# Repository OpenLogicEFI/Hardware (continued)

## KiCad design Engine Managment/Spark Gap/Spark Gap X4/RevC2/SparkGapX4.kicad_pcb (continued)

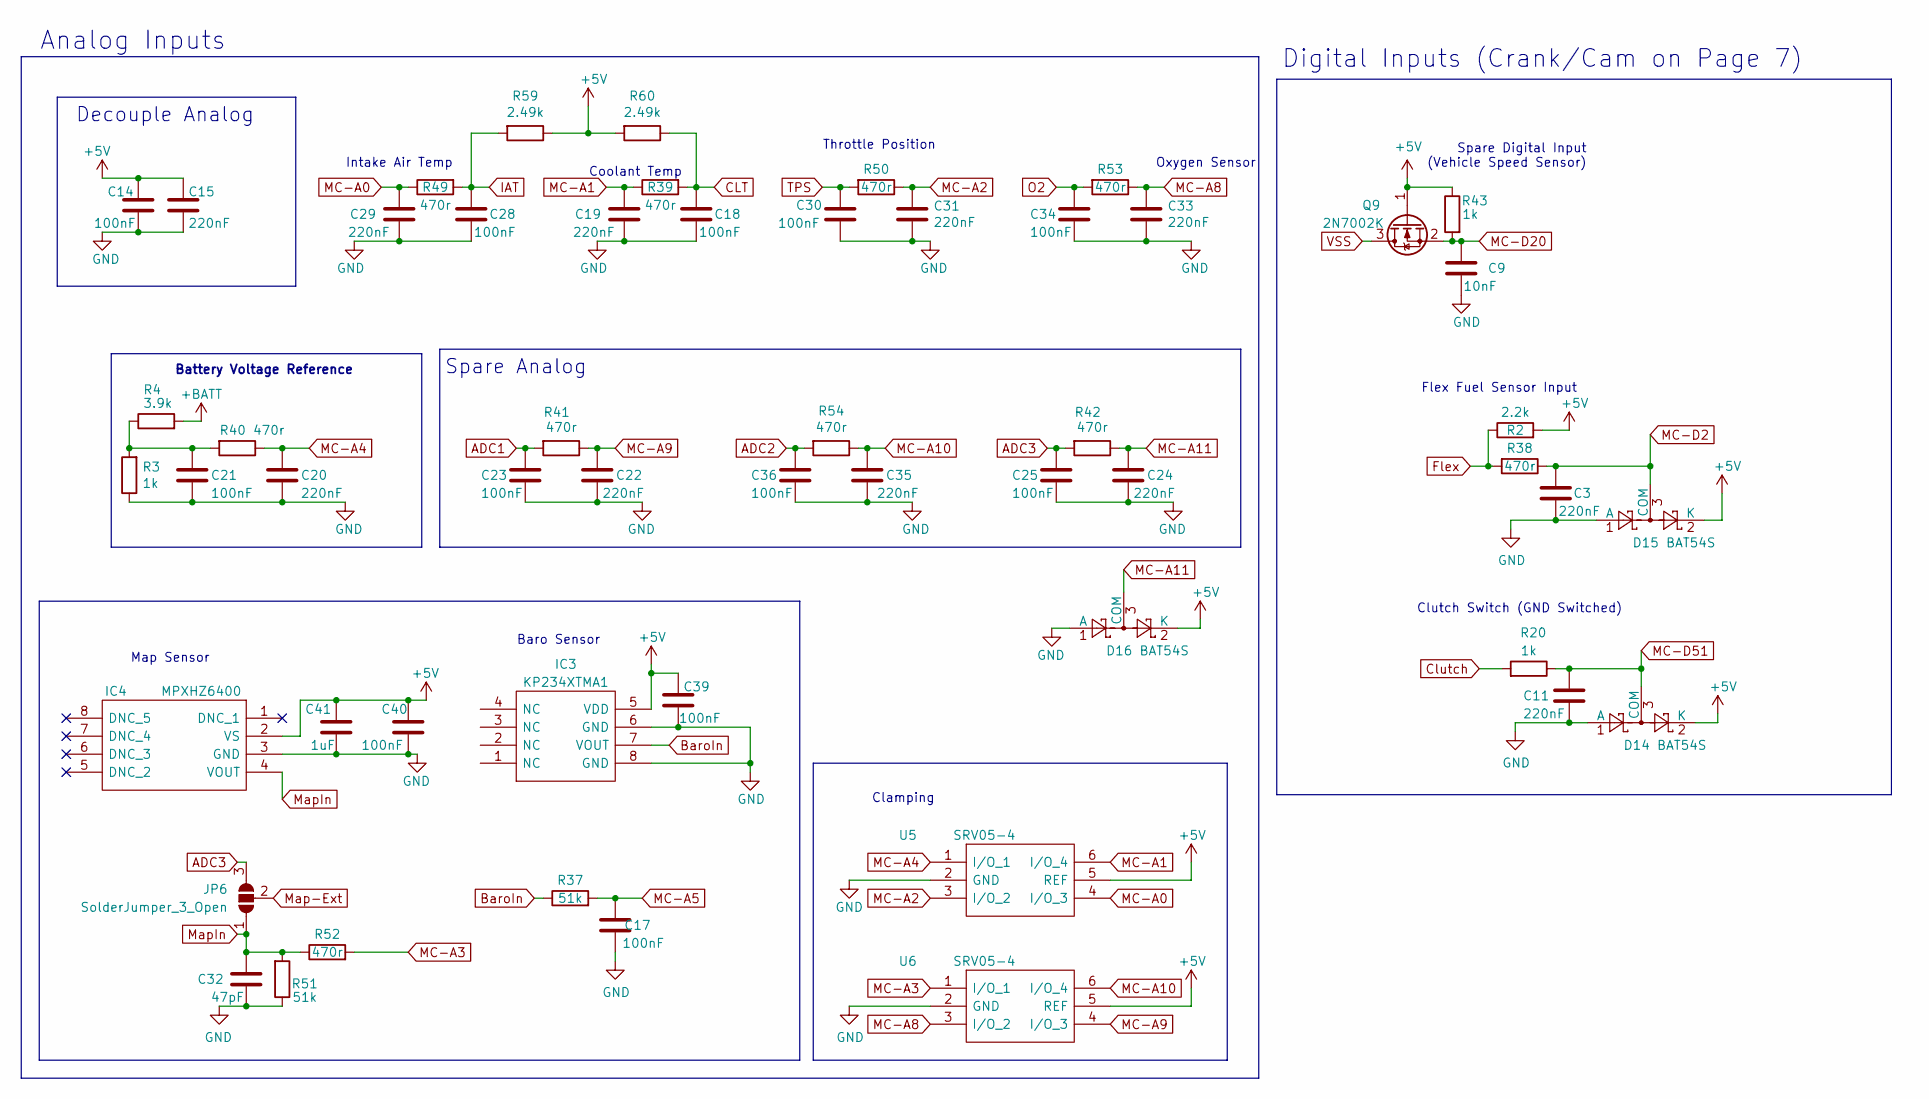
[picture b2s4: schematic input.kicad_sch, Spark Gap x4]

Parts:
C3, C11, C15, C19, C20, C22, C24, C29, C31, C33, C35: 220nF; C_0402_1005Metric; Manufacture Part Number CL05B224KO5NNNC; LCSC C16772
C9: 10nF; C_0402_1005Metric; Manufacture Part Number CL05B103KB5NNNC; LCSC C15195
C14, C17, C18, C21, C23, C25, C28, C30, C34, C36, C39, C40: 100nF; C_0402_1005Metric; Manufacture Part Number CL05B104KB54PNC; LCSC C307331
C32: 47pF; C_0402_1005Metric; Manufacture Part Number 0402CG470J500NT; LCSC C1567
C41: 1uF; C_0402_1005Metric; Manufacture Part Number CL05A105KA5NQNC; LCSC C52923
D14, D15, D16: BAT54S; SOT-23; Manufacture Part Number BAT54S; LCSC C7420333
IC3: KP234XTMA1; KP234-Handsoldering
IC4: MPXHZ6400; MPXHxxx_Handsoldering
JP6: SolderJumper_3_Open; SolderJumper-3-OPEN
Q9: 2N7002K; SOT-23; LCSC C22379475
R2: 2.2k; R_0402_1005Metric; Manufacture Part Number 0402WGF2201TCE; LCSC C25879
R3: 1k; R_0603_1608Metric; Manufacture Part Number 0603WAF1001T5E; LCSC C21190
R4: 3.9k; R_0603_1608Metric; Manufacture Part Number 0603WAF3901T5E; LCSC C23018
R20, R43: 1k; R_0402_1005Metric; Manufacture Part Number 0402WGF1001TCE; LCSC C11702
R37, R51: 51k; R_0402_1005Metric; Manufacture Part Number 0402WGF5102TCE; LCSC C25794
R38, R39, R40, R41, R42, R49, R50, R52, R53, R54: 470r; R_0402_1005Metric; Manufacture Part Number 0402WGF4700TCE; LCSC C25117
R59, R60: 2.49k; R_Axial_DIN0207_L6.3mm_D2.5mm_P7.62mm_Horizontal
U5, U6: SRV05-4; SOT-23-6; LCSC C2836319

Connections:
+5V: C14.1, C15.1, C39.1, C40.1, C41.1, D14.2 (K), D15.2 (K), D16.2 (K), IC3.5 (VDD), IC4.2 (VS), Q9.1 (G), R2.2, R43.1, R59.1, R60.2, U5.5 (REF), U6.5 (REF); also elsewhere on the board
+BATT: R4.2; also elsewhere on the board
ADC1: C23.1, R41.2; also elsewhere on the board
ADC2: C36.1, R54.2; also elsewhere on the board
ADC3: C25.1, JP6.3 (B), R42.2
BaroIn: IC3.7 (VOUT), R37.1
CLT: C18.1, R39.2, R60.1; also elsewhere on the board
Clutch: R20.2; also elsewhere on the board
Flex: R2.1, R38.2; also elsewhere on the board
GND: C3.2, C9.2, C11.2, C14.2, C15.2, C17.2, C18.2, C19.2, C20.2, C21.2, C22.2, C23.2, C24.2, C25.2, C28.2, C29.2, C30.2, C31.2, C32.2, C33.2, C34.2, C35.2, C36.2, C39.2, C40.2, C41.2, D14.1 (A), D15.1 (A), D16.1 (A), IC3.6 (GND), IC3.8 (GND), IC4.3 (GND), R3.1, R51.1, U5.2 (GND), U6.2 (GND); also elsewhere on the board
IAT: C28.1, R49.2, R59.2; also elsewhere on the board
MC-A0: C29.1, R49.1, U5.4 (I/O_3); also elsewhere on the board
MC-A1: C19.1, R39.1, U5.6 (I/O_4); also elsewhere on the board
MC-A2: C31.1, R50.1, U5.3 (I/O_2); also elsewhere on the board
MC-A3: R52.2, U6.1 (I/O_1); also elsewhere on the board
MC-A4: C20.1, R40.1, U5.1 (I/O_1); also elsewhere on the board
MC-A5: C17.1, R37.2; also elsewhere on the board
MC-A8: C33.1, R53.1, U6.3 (I/O_2); also elsewhere on the board
MC-A9: C22.1, R41.1, U6.4 (I/O_3); also elsewhere on the board
MC-A10: C35.1, R54.1, U6.6 (I/O_4); also elsewhere on the board
MC-A11: C24.1, D16.3 (COM), R42.1; also elsewhere on the board
MC-D2: C3.1, D15.3 (COM), R38.1; also elsewhere on the board
MC-D20: C9.1, Q9.2 (S), R43.2; also elsewhere on the board
MC-D51: C11.1, D14.3 (COM), R20.1; also elsewhere on the board
Map-Ext: JP6.2 (C); also elsewhere on the board
MapIn: C32.1, IC4.4 (VOUT), JP6.1 (A), R51.2, R52.1
unnamed: C21.1, R3.2, R4.1, R40.2
O2: C34.1, R53.2; also elsewhere on the board
TPS: C30.1, R50.2; also elsewhere on the board
VSS: Q9.3 (D); also elsewhere on the board

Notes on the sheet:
Map Sensor
Clutch Switch (GND Switched)
Analog Inputs
Throttle Position
Spare Digital Input (Vehicle Speed Sensor)
Oxygen Sensor
Digital Inputs (Crank/Cam on Page 7)
Coolant Temp
Intake Air Temp
Baro Sensor
Battery Voltage Reference
Spare Analog
Flex Fuel Sensor Input
Decouple Analog
Clamping

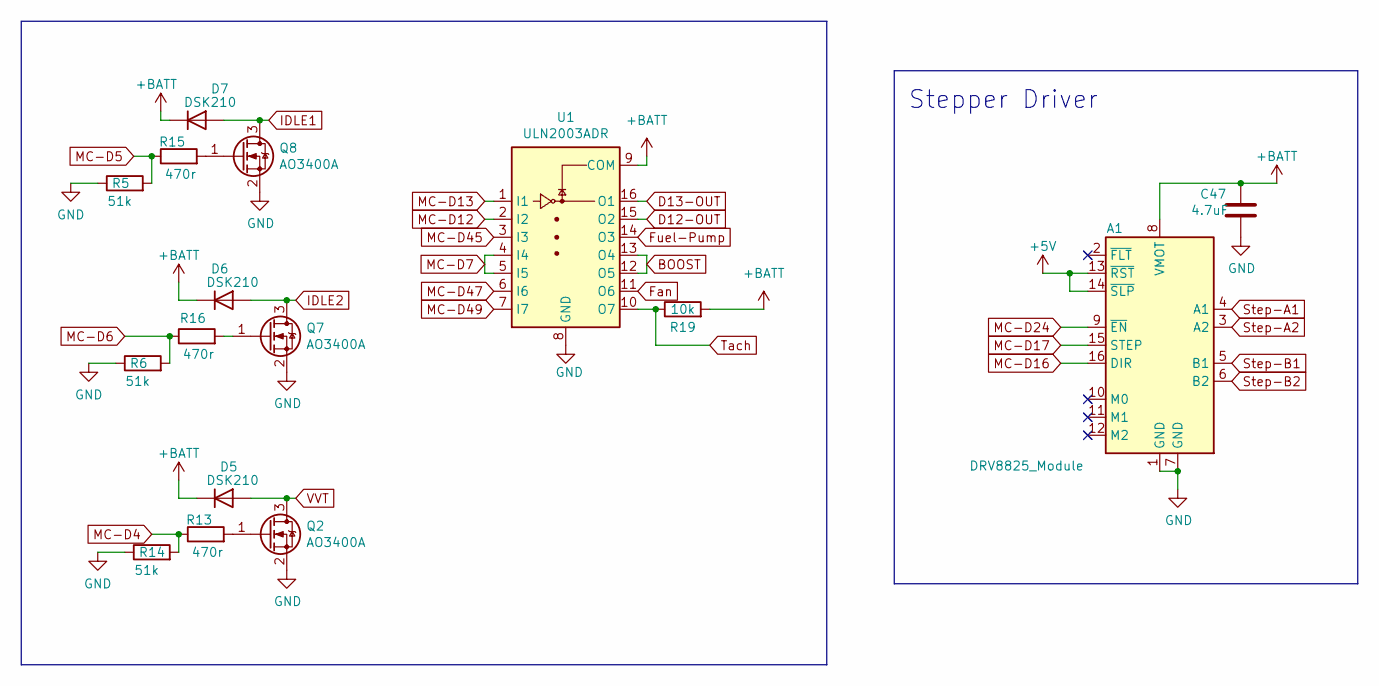
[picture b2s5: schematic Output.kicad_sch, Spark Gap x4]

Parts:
A1: DRV8825_Module; DVR8825-Labeled-Front
C47: 4.7uF; C_1206_3216Metric; Manufacture Part Number 1206B475K500NT; LCSC C29823
D5, D6, D7: DSK210; D_SOD-123F; Manufacture Part Number DSK210; LCSC C7502713
Q2, Q7, Q8: AO3400A; SOT-23; LCSC C20917
R5, R6, R14: 51k; R_0402_1005Metric; Manufacture Part Number 0402WGF5102TCE; LCSC C25794
R13, R15, R16: 470r; R_0402_1005Metric; Manufacture Part Number 0402WGF4700TCE; LCSC C25117
R19: 10k; R_0402_1005Metric; Manufacture Part Number 0402WGF1002TCE; LCSC C25744
U1: ULN2003ADR; SOIC-16_3.9x9.9mm_P1.27mm; Manufacture Part Number ULN2003ADR; LCSC C7512

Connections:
+5V: A1.13 (~RST), A1.14 (~SLP); also elsewhere on the board
+BATT: A1.8 (VMOT), C47.1, D5.1 (K), D6.1 (K), D7.1 (K), R19.2, U1.9 (COM); also elsewhere on the board
BOOST: U1.12 (O5), U1.13 (O4); also elsewhere on the board
D12-OUT: U1.15 (O2); also elsewhere on the board
D13-OUT: U1.16 (O1); also elsewhere on the board
Fan: U1.11 (O6); also elsewhere on the board
Fuel-Pump: U1.14 (O3); also elsewhere on the board
GND: A1.1 (GND), A1.7 (GND), C47.2, Q2.2 (S), Q7.2 (S), Q8.2 (S), R5.1, R6.1, R14.1, U1.8 (GND); also elsewhere on the board
IDLE1: A1.6 (B2), D7.2 (A), Q8.3 (D); also elsewhere on the board
IDLE2: A1.5 (B1), D6.2 (A), Q7.3 (D); also elsewhere on the board
MC-D4: R13.1, R14.2; also elsewhere on the board
MC-D5: R5.2, R15.1; also elsewhere on the board
MC-D6: R6.2, R16.1; also elsewhere on the board
MC-D7: U1.4 (I4), U1.5 (I5); also elsewhere on the board
MC-D12: U1.2 (I2); also elsewhere on the board
MC-D13: U1.1 (I1); also elsewhere on the board
MC-D16: A1.16 (DIR); also elsewhere on the board
MC-D17: A1.15 (STEP); also elsewhere on the board
MC-D24: A1.9 (~EN); also elsewhere on the board
MC-D45: U1.3 (I3); also elsewhere on the board
MC-D47: U1.6 (I6); also elsewhere on the board
MC-D49: U1.7 (I7); also elsewhere on the board
unnamed: Q2.1 (G), R13.2
unnamed: Q7.1 (G), R16.2
unnamed: Q8.1 (G), R15.2
Step-A1: A1.4 (A1); also elsewhere on the board
Step-A2: A1.3 (A2); also elsewhere on the board
Tach: R19.1, U1.10 (O7); also elsewhere on the board
VVT: D5.2 (A), Q2.3 (D); also elsewhere on the board

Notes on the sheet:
Stepper Driver

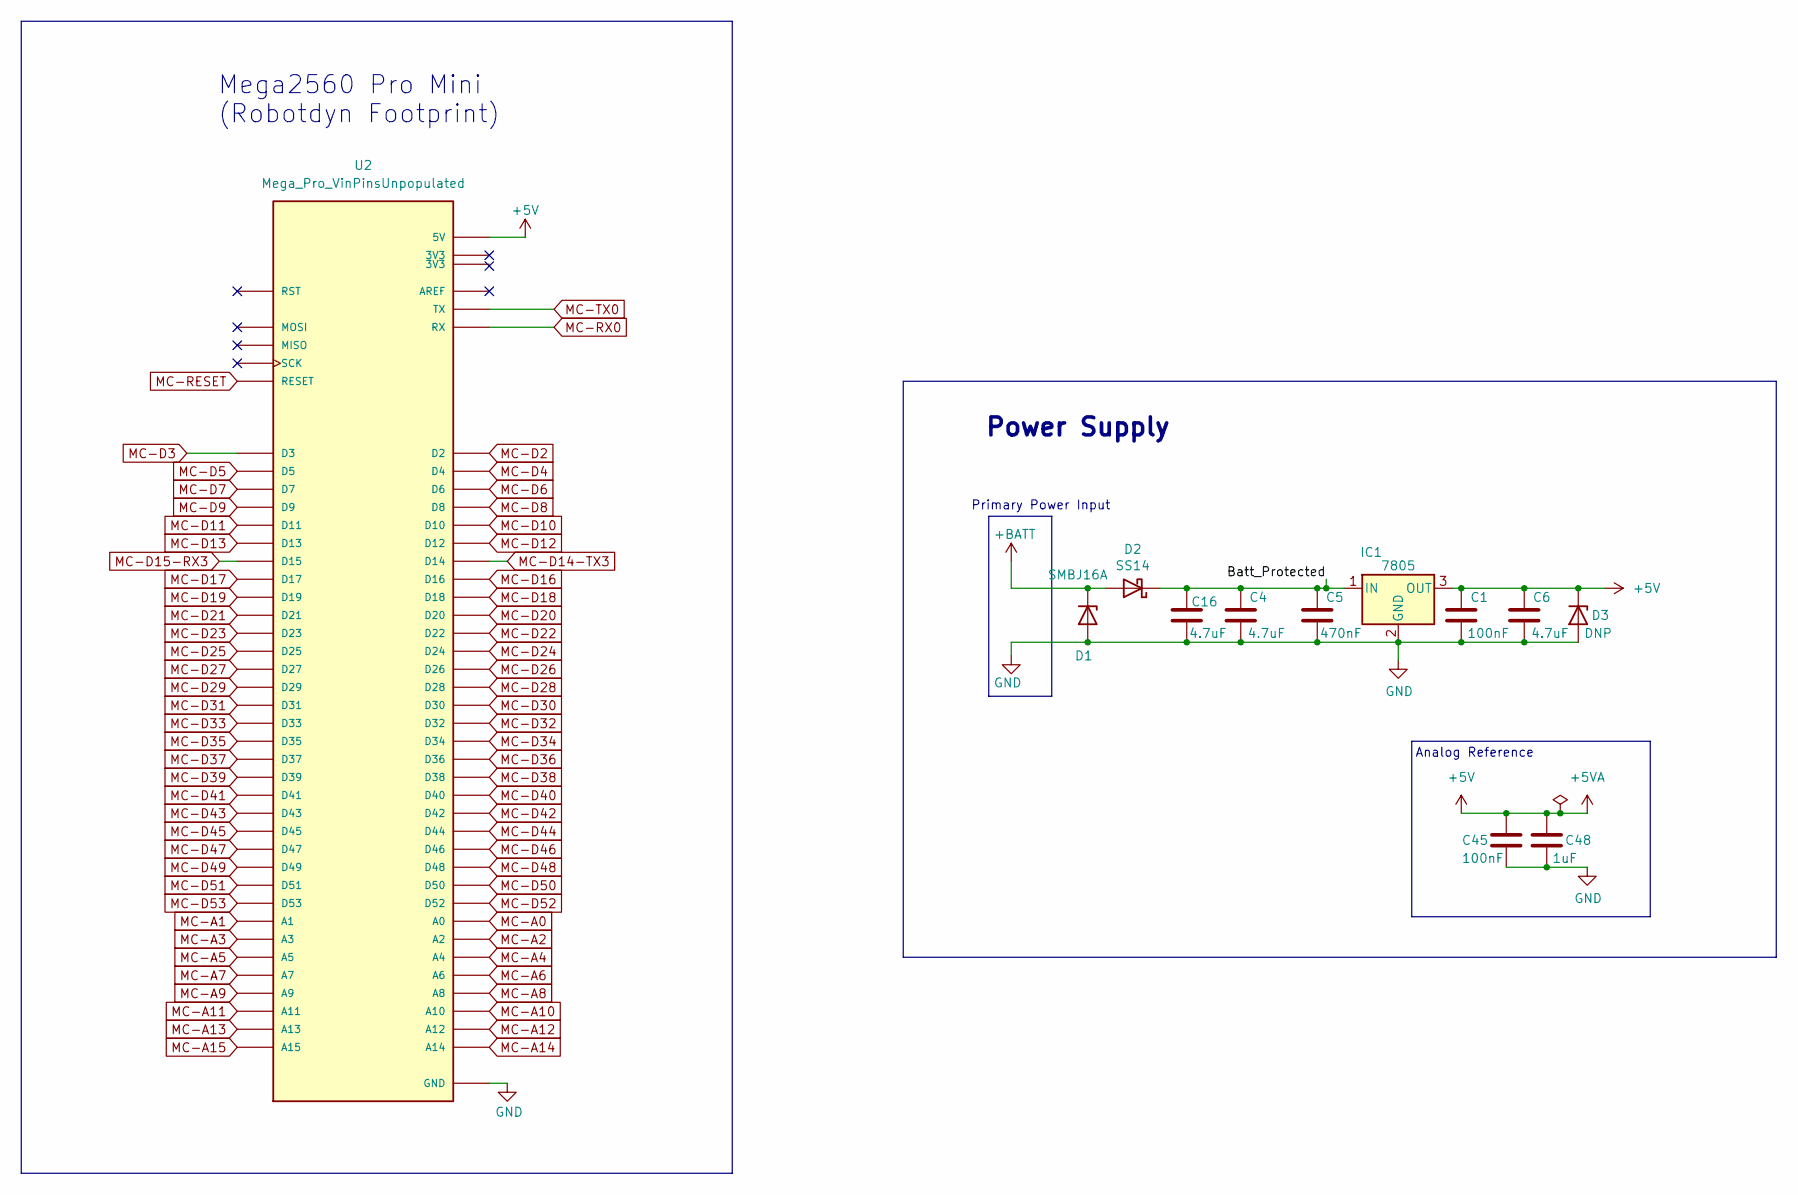
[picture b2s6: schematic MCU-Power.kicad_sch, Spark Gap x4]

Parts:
C1, C45: 100nF; C_0402_1005Metric; Manufacture Part Number CL05B104KB54PNC; LCSC C307331
C4, C6, C16: 4.7uF; C_1206_3216Metric; Manufacture Part Number 1206B475K500NT; LCSC C29823
C5: 470nF; C_0805_2012Metric; Manufacture Part Number CL21B474KBFNNNE; LCSC C13967
C48: 1uF; C_0402_1005Metric; Manufacture Part Number CL05A105KA5NQNC; LCSC C52923
D1: SMBJ16A; D_SMB; Manufacture Part Number SMBJ16A; LCSC C19077571
D2: SS14; D_SMA; Manufacture Part Number SS14; LCSC C2480
D3: DNP; D_SOD-323; Manufacture Part Number MMSZ5232BS; LCSC C22395563
IC1: 7805; TO-220-3_Vertical_SmallCrtYrd
U2: Mega_Pro_VinPinsUnpopulated; Arduino_Mega_Mini_2560_SmallCrtYd_NoVin

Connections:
+5V: C1.1, C6.1, C45.1, C48.1, D3.1 (K), IC1.3 (OUT), U2.5V_1 (5V), U2.5V_2 (5V), U2.5V_3 (5V); also elsewhere on the board
+BATT: D1.1 (K), D2.2 (A); also elsewhere on the board
/MCU and Power/Batt_Protected: C4.1, C5.1, C16.1, D2.1 (K), IC1.1 (IN)
GND: C1.2, C4.2, C5.2, C6.2, C16.2, C45.2, C48.2, D1.2 (A), D3.2 (A), IC1.2 (GND), U2.GND_1 (GND), U2.GND_2 (GND), U2.GND_3 (GND); also elsewhere on the board
MC-A0: U2.A0; also elsewhere on the board
MC-A1: U2.A1; also elsewhere on the board
MC-A2: U2.A2; also elsewhere on the board
MC-A3: U2.A3; also elsewhere on the board
MC-A4: U2.A4; also elsewhere on the board
MC-A5: U2.A5; also elsewhere on the board
MC-A6: U2.A6
MC-A7: U2.A7
MC-A8: U2.A8; also elsewhere on the board
MC-A9: U2.A9; also elsewhere on the board
MC-A10: U2.A10; also elsewhere on the board
MC-A11: U2.A11; also elsewhere on the board
MC-A12: U2.A12
MC-A13: U2.A13
MC-A14: U2.A14
MC-A15: U2.A15
MC-D2: U2.D2; also elsewhere on the board
MC-D3: U2.D3; also elsewhere on the board
MC-D4: U2.D4; also elsewhere on the board
MC-D5: U2.D5; also elsewhere on the board
MC-D6: U2.D6; also elsewhere on the board
MC-D7: U2.D7; also elsewhere on the board
MC-D8: U2.D8; also elsewhere on the board
MC-D9: U2.D9; also elsewhere on the board
MC-D10: U2.D10; also elsewhere on the board
MC-D11: U2.D11; also elsewhere on the board
MC-D12: U2.D12; also elsewhere on the board
MC-D13: U2.D13; also elsewhere on the board
MC-D14-TX3: U2.D14; also elsewhere on the board
MC-D15-RX3: U2.D15; also elsewhere on the board
MC-D16: U2.D16; also elsewhere on the board
MC-D17: U2.D17; also elsewhere on the board
MC-D18: U2.D18; also elsewhere on the board
MC-D19: U2.D19; also elsewhere on the board
MC-D20: U2.D20; also elsewhere on the board
MC-D21: U2.D21
MC-D22: U2.D22
MC-D23: U2.D23
MC-D24: U2.D24; also elsewhere on the board
MC-D25: U2.D25
MC-D26: U2.D26
MC-D27: U2.D27
MC-D28: U2.D28
MC-D29: U2.D29
MC-D30: U2.D30
MC-D31: U2.D31
MC-D32: U2.D32
MC-D33: U2.D33
MC-D34: U2.D34
MC-D35: U2.D35
MC-D36: U2.D36
MC-D37: U2.D37
MC-D38: U2.D38; also elsewhere on the board
MC-D39: U2.D39
MC-D40: U2.D40; also elsewhere on the board
MC-D41: U2.D41
MC-D42: U2.D42
MC-D43: U2.D43
MC-D44: U2.D44
MC-D45: U2.D45; also elsewhere on the board
MC-D46: U2.D46
MC-D47: U2.D47; also elsewhere on the board
MC-D48: U2.D48
MC-D49: U2.D49; also elsewhere on the board
MC-D50: U2.D50; also elsewhere on the board
MC-D51: U2.D51; also elsewhere on the board
MC-D52: U2.D52; also elsewhere on the board
MC-D53: U2.D53
MC-RESET: U2.RESET; also elsewhere on the board
MC-RX0: U2.RX; also elsewhere on the board
MC-TX0: U2.TX; also elsewhere on the board

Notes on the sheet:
Primary Power Input
Power Supply
Analog Reference
Mega2560 Pro Mini (Robotdyn Footprint)

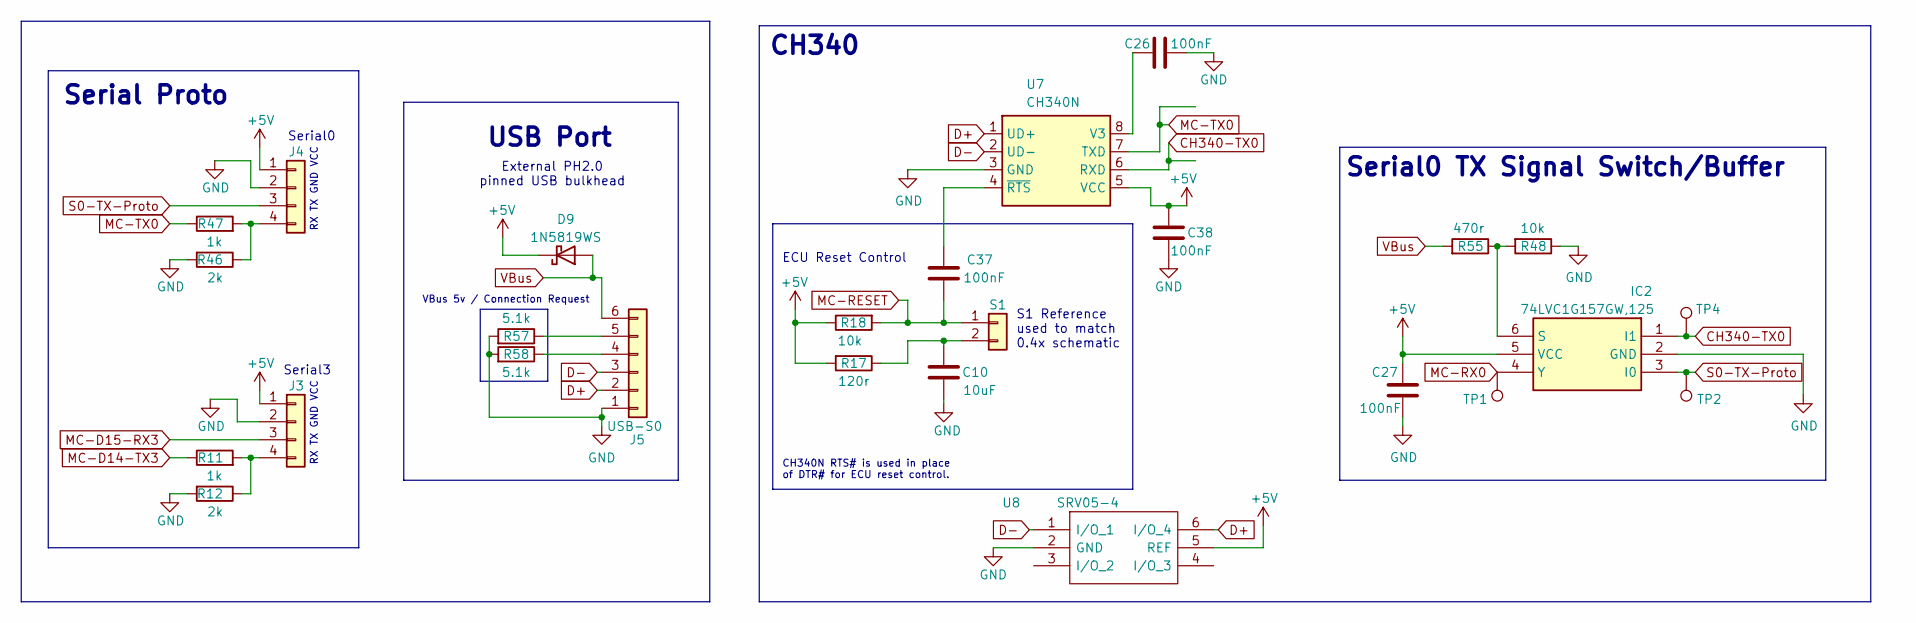
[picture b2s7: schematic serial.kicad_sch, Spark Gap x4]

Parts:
C10: 10uF; C_0603_1608Metric; Manufacture Part Number CL10A106KP8NNNC; LCSC C19702
C26, C27, C37, C38: 100nF; C_0402_1005Metric; Manufacture Part Number CL05B104KB54PNC; LCSC C307331
D9: 1N5819WS; D_SOD-323; Manufacture Part Number 1N5819WS; LCSC C7420326
IC2: 74LVC1G157GW,125; SOP65P210X110-6N; Manufacture Part Number 74LVC1G157GW,125; LCSC C135822
J3, J4: Conn_01x04; 1X4-PROTO-NoSilk
J5: USB-S0; JST_PH_B6B-PH-K_1x06_P2.00mm_Vertical
R11, R47: 1k; R_0402_1005Metric; Manufacture Part Number 0402WGF1001TCE; LCSC C11702
R12, R46: 2k; R_0402_1005Metric; Manufacture Part Number 0402WGF2001TCE; LCSC C4109
R17: 120r; R_0603_1608Metric; Manufacture Part Number 0402WGF4700TCE; LCSC C22787
R18, R48: 10k; R_0402_1005Metric; Manufacture Part Number 0402WGF1002TCE; LCSC C25744
R55: 470r; R_0402_1005Metric; Manufacture Part Number 0402WGF4700TCE; LCSC C25117
R57, R58: 5.1k; R_0402_1005Metric; Manufacture Part Number 0402WGF5101TCE; LCSC C25905
S1: Reset Control; PinHeader_1x02_P2.54mm_Horizontal
TP1, TP2, TP4: TestPoint; TestPoint_THT_D0.6mm_Drill0.3mm
U7: CH340N; SOIC-8_3.9x4.9mm_P1.27mm; LCSC C2977777
U8: SRV05-4; SOT-23-6; LCSC C2836319

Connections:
+5V: C27.2, C38.1, D9.1 (K), IC2.5 (VCC), J3.1, J4.1, R17.2, R18.1, U7.5 (VCC), U8.5 (REF); also elsewhere on the board
CH340-TX0: IC2.1 (I1), TP4.1 (1_1), U7.6 (RXD)
D+: J5.2, U7.1 (UD+), U8.6 (I/O_4)
D-: J5.3, U7.2 (UD-), U8.1 (I/O_1)
GND: C10.2, C26.2, C27.1, C38.2, IC2.2 (GND), J3.2, J4.2, J5.1, R12.2, R46.2, R48.1, R57.2, R58.2, U7.3 (GND), U8.2 (GND); also elsewhere on the board
MC-D14-TX3: R11.1; also elsewhere on the board
MC-D15-RX3: J3.3; also elsewhere on the board
MC-RESET: C37.2, R18.2, S1.1; also elsewhere on the board
MC-RX0: IC2.4 (Y), TP1.1 (1_1); also elsewhere on the board
MC-TX0: R47.1, U7.7 (TXD); also elsewhere on the board
unnamed: IC2.6 (S), R48.2, R55.1
unnamed: J3.4, R11.2, R12.1
unnamed: J4.4, R46.1, R47.2
unnamed: J5.4, R58.1
unnamed: J5.5, R57.1
unnamed: C10.1, R17.1, S1.2
unnamed: C26.1, U7.8 (V3)
unnamed: C37.1, U7.4 (~RTS)
S0-TX-Proto: IC2.3 (I0), J4.3, TP2.1 (1_1)
VBus: D9.2 (A), J5.6, R55.2

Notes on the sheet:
CH340
RX TX GND VCC
Serial3
S1 Reference used to match 0.4x schematic
External PH2.0 pinned USB bulkhead
Serial0
ECU Reset Control
VBus 5v / Connection Request
Serial0 TX Signal Switch/Buffer
USB Port
CH340N RTS# is used in place of DTR# for ECU reset control.
Serial Proto

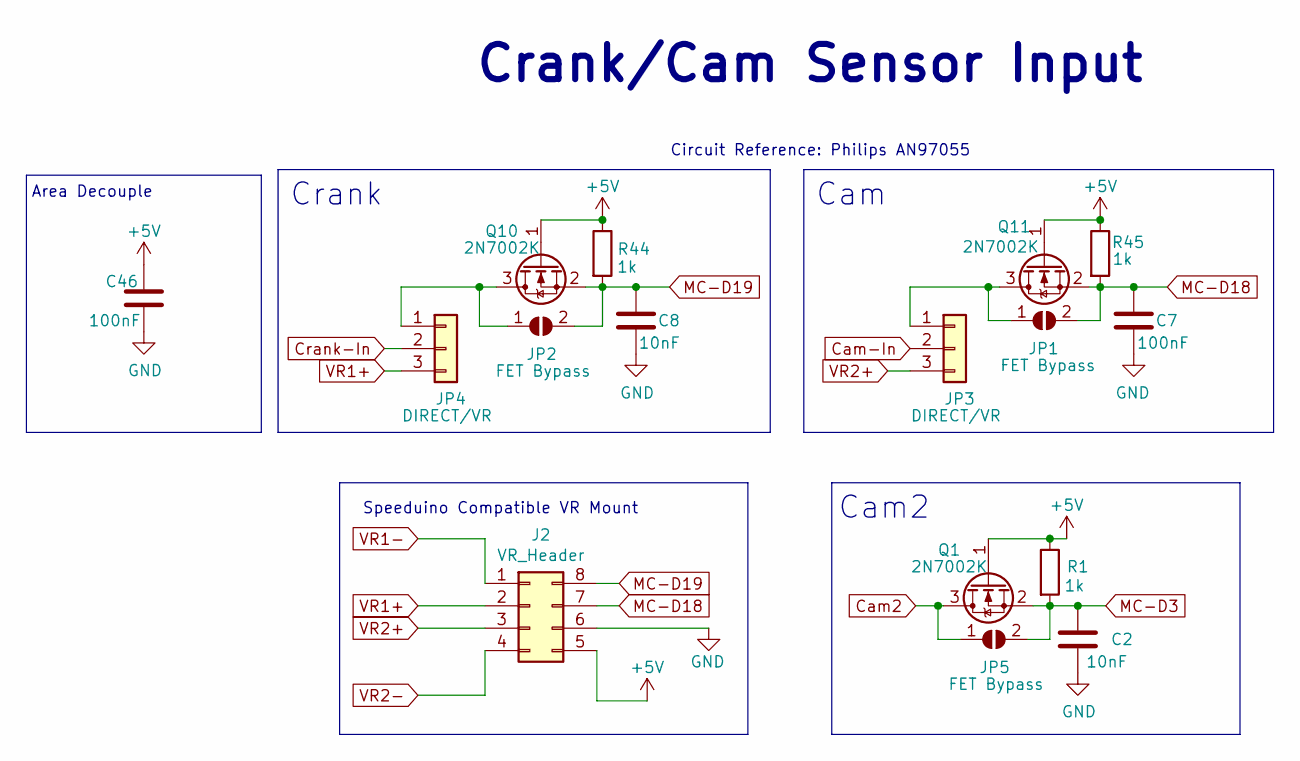
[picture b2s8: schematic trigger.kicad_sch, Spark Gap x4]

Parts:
C2, C8: 10nF; C_0402_1005Metric; Manufacture Part Number CL05B103KB5NNNC; LCSC C15195
C7, C46: 100nF; C_0402_1005Metric; Manufacture Part Number CL05B104KB54PNC; LCSC C307331
J2: VR_Header; Socket_VRConditioner_Corrected
JP1, JP2, JP5: FET Bypass; SolderJumper-2_P1.3mm_Open_RoundedPad1.0x1.5mm
JP3, JP4: DIRECT/VR; 1x03-Proto
Q1, Q10, Q11: 2N7002K; SOT-23; LCSC C22379475
R1, R44, R45: 1k; R_0402_1005Metric; Manufacture Part Number 0402WGF1001TCE; LCSC C11702

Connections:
+5V: C46.1, J2.5, Q1.1 (G), Q10.1 (G), Q11.1 (G), R1.1, R44.1, R45.1; also elsewhere on the board
Cam2: JP5.1 (A), Q1.3 (D); also elsewhere on the board
Cam-In: JP3.2; also elsewhere on the board
Crank-In: JP4.2; also elsewhere on the board
GND: C2.1, C7.1, C8.1, C46.2, J2.6; also elsewhere on the board
MC-D3: C2.2, JP5.2 (B), Q1.2 (S), R1.2; also elsewhere on the board
MC-D18: C7.2, J2.7, JP1.2 (B), Q11.2 (S), R45.2; also elsewhere on the board
MC-D19: C8.2, J2.8, JP2.2 (B), Q10.2 (S), R44.2; also elsewhere on the board
unnamed: JP1.1 (A), JP3.1, Q11.3 (D)
unnamed: JP2.1 (A), JP4.1, Q10.3 (D)
VR1+: J2.2, JP4.3
VR1-: J2.1; also elsewhere on the board
VR2+: J2.3, JP3.3
VR2-: J2.4; also elsewhere on the board

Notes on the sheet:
Crank/Cam Sensor Input
Cam2
Cam
Speeduino Compatible VR Mount
Area Decouple
Circuit Reference: Philips AN97055
Crank

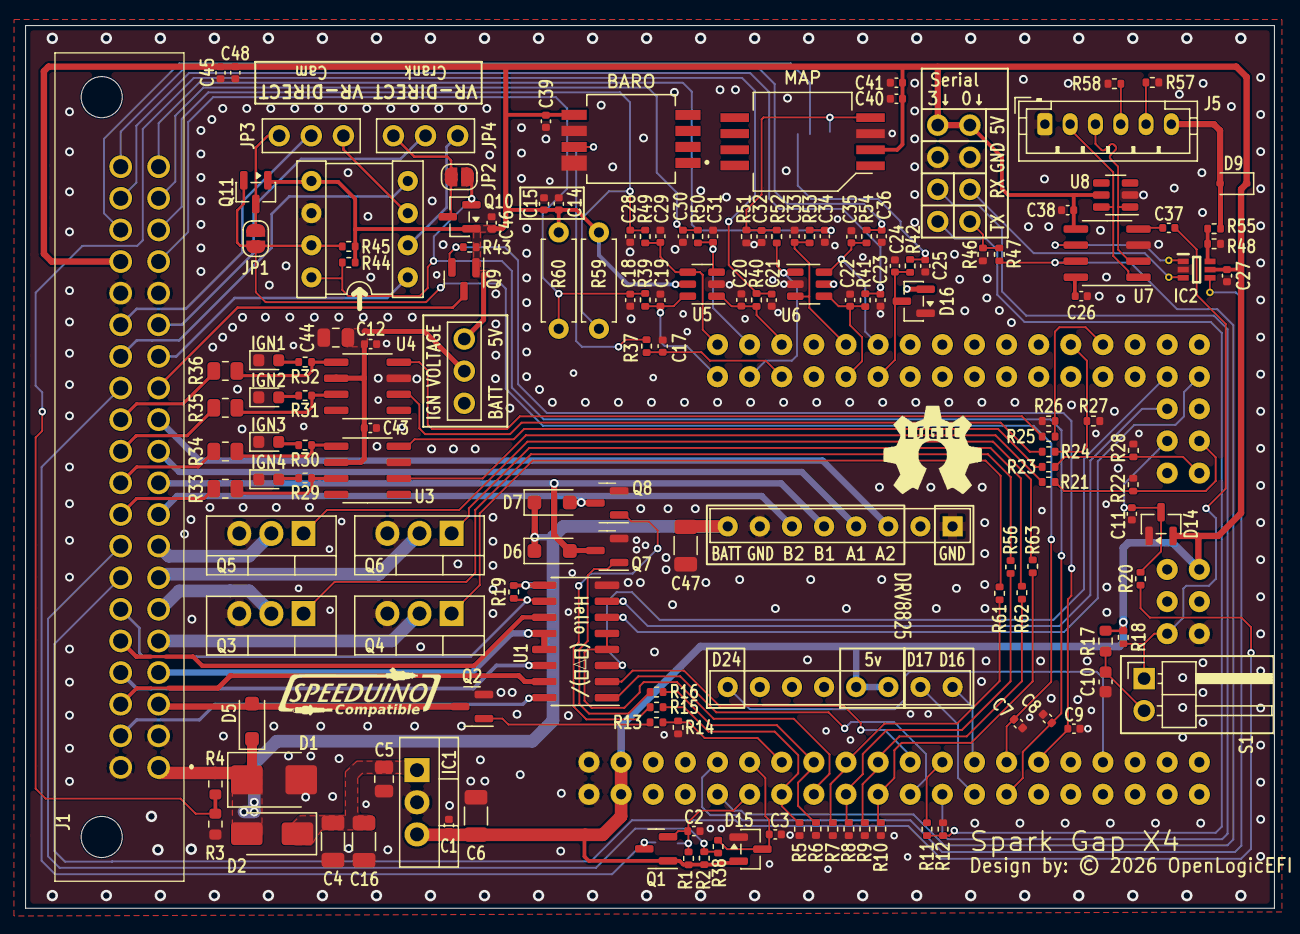
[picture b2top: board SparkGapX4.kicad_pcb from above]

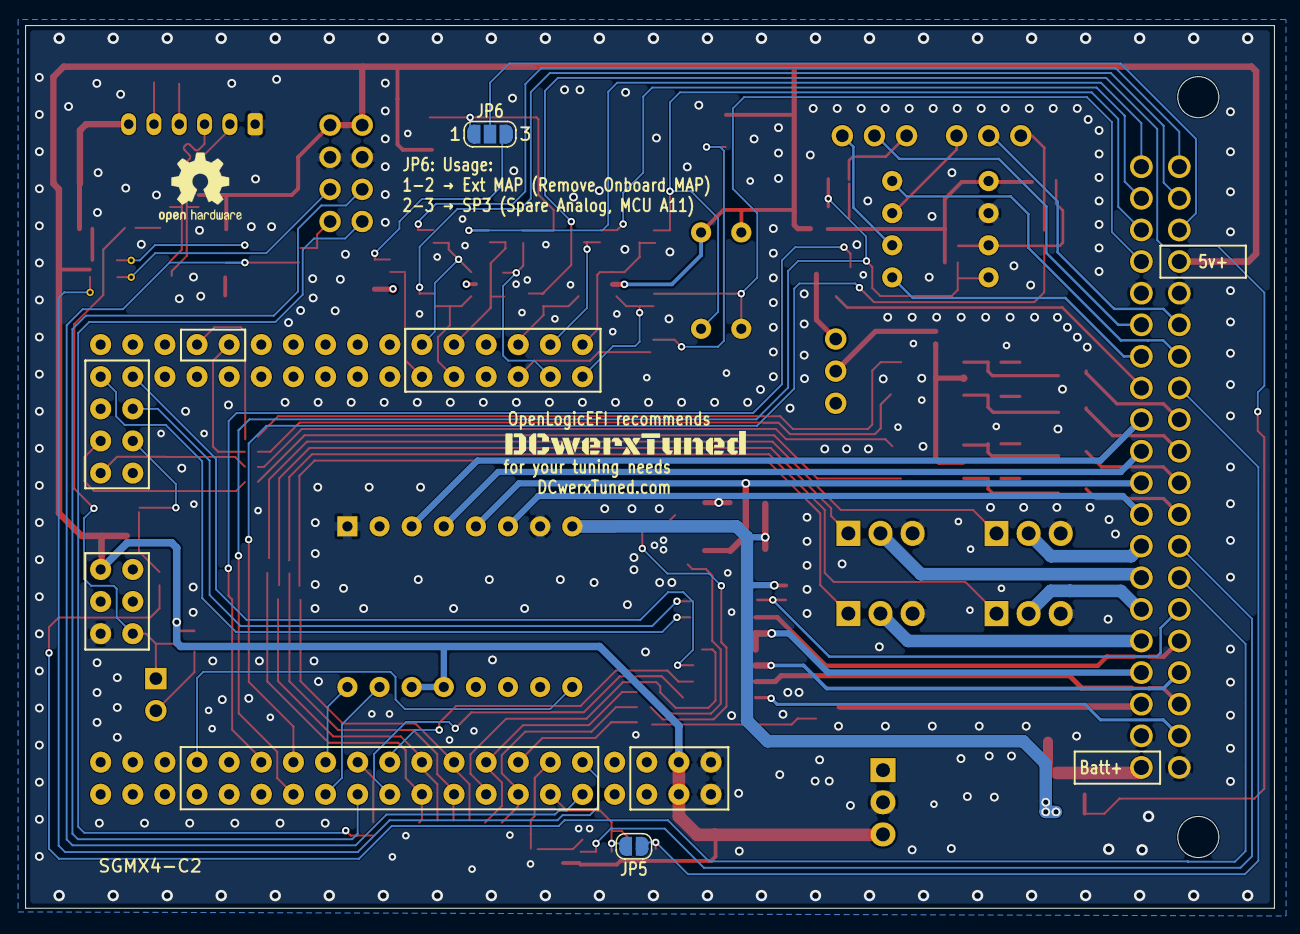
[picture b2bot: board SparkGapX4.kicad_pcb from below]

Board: 4 copper layers, 98.8 x 69.8 mm, 164 parts (3 on the bottom side), 120 nets.

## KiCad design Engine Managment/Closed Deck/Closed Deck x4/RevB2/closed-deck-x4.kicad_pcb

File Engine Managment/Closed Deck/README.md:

# ClosedDeck

ClosedDeck is a hardware shield designed to use an Arduino Mega as the central microcontroller unit (MCU), thereby enabling it to operate as a standalone engine management system. This functionality is achieved when the shield is coupled with compatible firmware from an open-source project called Speeduino, developed by Josh Stewart.

www.OpenLogicEFI.com

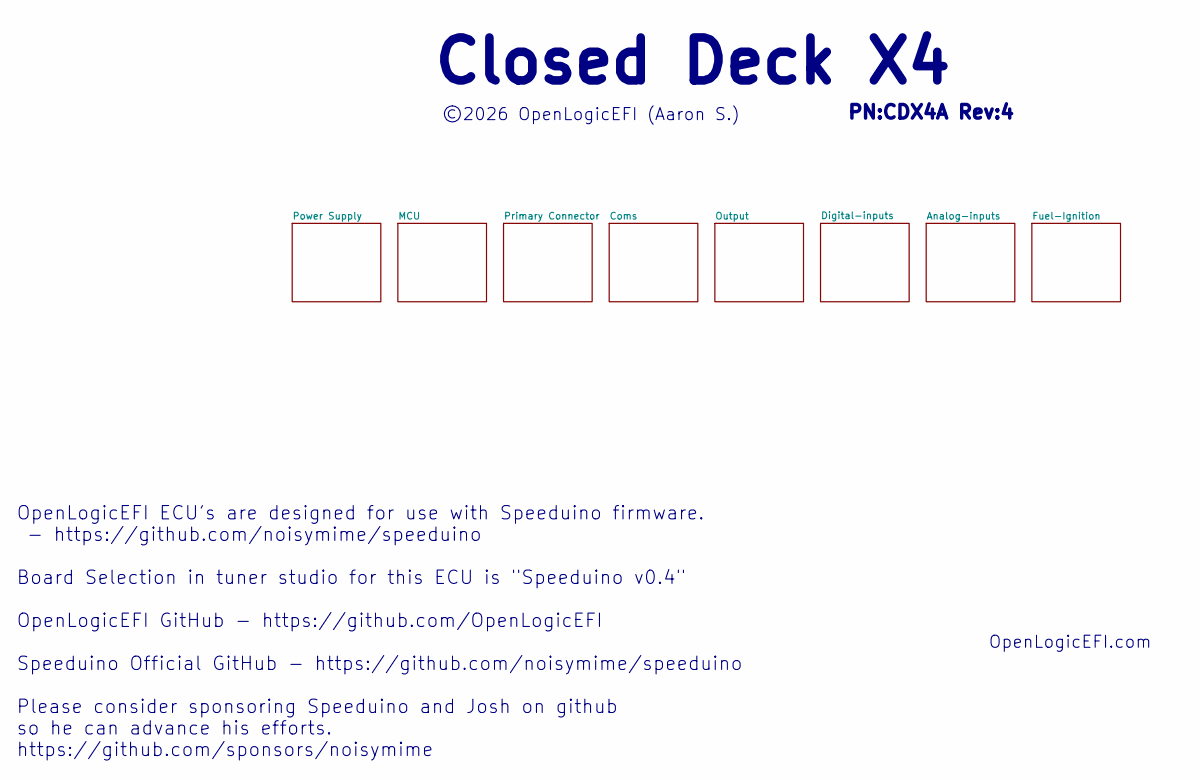
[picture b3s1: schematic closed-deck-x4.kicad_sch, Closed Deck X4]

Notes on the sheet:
©2026 OpenLogicEFI (Aaron S.)
OpenLogicEFI ECU's are designed for use with Speeduino firmware. - https://github.com/noisymime/speeduino Board Selection in tuner studio for this ECU is "Speeduino v0.4" OpenLogicEFI GitHub - https://github.com/OpenLogicEFI Speeduino Official GitHub - https://github.com/noisymime/speeduino Please 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
Closed Deck X4
PN:CDX4A Rev:4
OpenLogicEFI.com

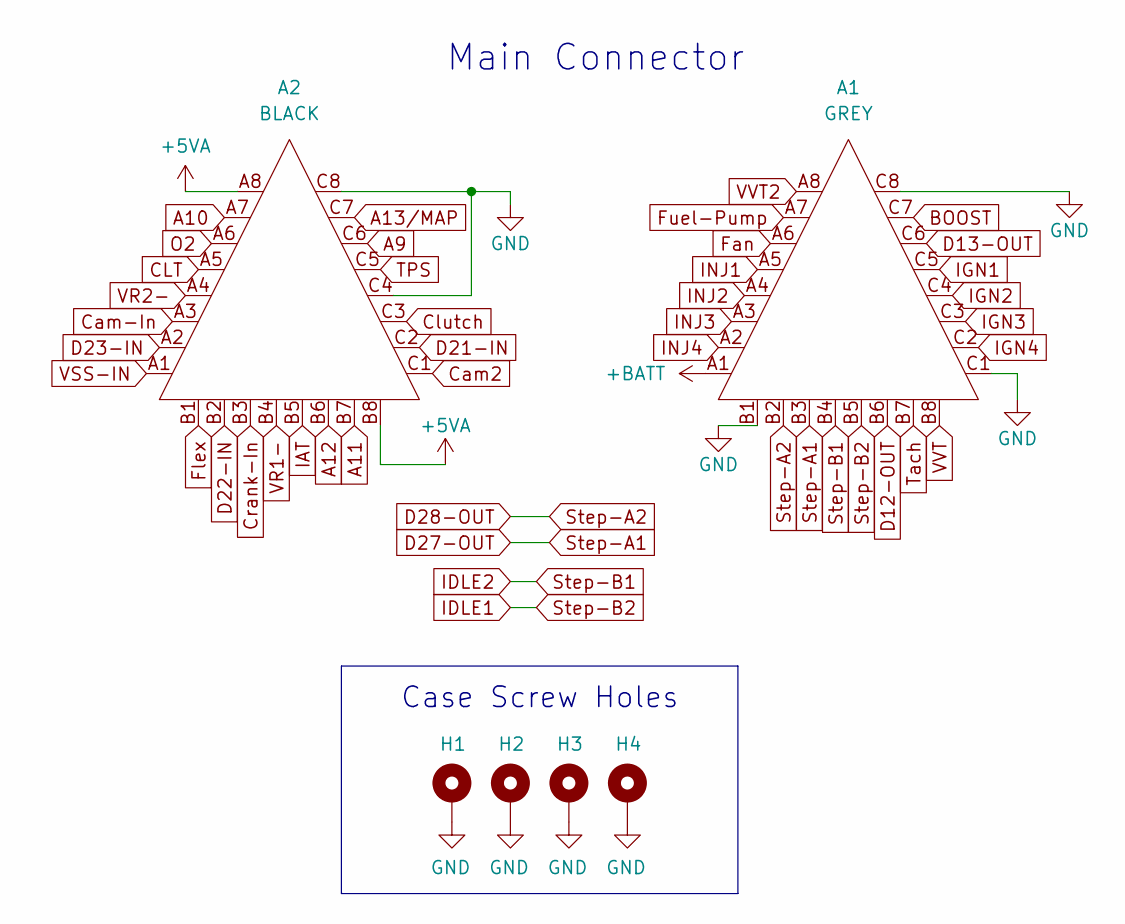
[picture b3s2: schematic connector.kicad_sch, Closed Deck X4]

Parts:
A1: GREY; Delphi_Sicma_24_Grey
A2: BLACK; Delphi_Sicma_24_Black
H1, H2, H3, H4: MountingHole_Pad; MountingHole_3.5mm_Pad

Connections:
+5VA: A2.A8, A2.B8; also elsewhere on the board
+BATT: A1.A1; also elsewhere on the board
A9: A2.C6; also elsewhere on the board
A10: A2.A7; also elsewhere on the board
A11: A2.B7; also elsewhere on the board
A12: A2.B6; also elsewhere on the board
A13/MAP: A2.C7; also elsewhere on the board
BOOST: A1.C7; also elsewhere on the board
CLT: A2.A5; also elsewhere on the board
Cam2: A2.C1; also elsewhere on the board
Cam-In: A2.A3; also elsewhere on the board
Clutch: A2.C3; also elsewhere on the board
Crank-In: A2.B3; also elsewhere on the board
D12-OUT: A1.B6; also elsewhere on the board
D13-OUT: A1.C6; also elsewhere on the board
D21-IN: A2.C2; also elsewhere on the board
D22-IN: A2.B2; also elsewhere on the board
D23-IN: A2.A2; also elsewhere on the board
D27-OUT: A1.B3; also elsewhere on the board
D28-OUT: A1.B2; also elsewhere on the board
Fan: A1.A6; also elsewhere on the board
Flex: A2.B1; also elsewhere on the board
Fuel-Pump: A1.A7; also elsewhere on the board
GND: A1.B1, A1.C1, A1.C8, A2.C4, A2.C8, H1.1 (1_1), H2.1 (1_1), H3.1 (1_1), H4.1 (1_1); also elsewhere on the board
IAT: A2.B5; also elsewhere on the board
IDLE1: A1.B5; also elsewhere on the board
IDLE2: A1.B4; also elsewhere on the board
IGN1: A1.C5; also elsewhere on the board
IGN2: A1.C4; also elsewhere on the board
IGN3: A1.C3; also elsewhere on the board
IGN4: A1.C2; also elsewhere on the board
INJ1: A1.A5; also elsewhere on the board
INJ2: A1.A4; also elsewhere on the board
INJ3: A1.A3; also elsewhere on the board
INJ4: A1.A2; also elsewhere on the board
O2: A2.A6; also elsewhere on the board
TPS: A2.C5; also elsewhere on the board
Tach: A1.B7; also elsewhere on the board
VR1-: A2.B4; also elsewhere on the board
VR2-: A2.A4; also elsewhere on the board
VSS-IN: A2.A1; also elsewhere on the board
VVT: A1.B8; also elsewhere on the board
VVT2: A1.A8; also elsewhere on the board

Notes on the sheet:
Case Screw Holes
Main Connector
